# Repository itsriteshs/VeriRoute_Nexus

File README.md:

# PacketFlow ImmuneNet

**TCP/IP for parcels, with an immune system for trust.**

PacketFlow ImmuneNet is a trust-aware logistics protocol for FAR AWAY 2026 Round 1. Modern logistics systems often track claims that a parcel moved. PacketFlow ImmuneNet verifies whether each movement could physically have happened using scan identity, GPS/geofence proof, timestamp and speed plausibility, route graph validity, temperature state, tamper state, hub trust, and live rerouting.

The MVP combines a FastAPI backend, a React/Vite digital twin dashboard, deterministic simulation scenarios, an event ledger, WebSocket live updates, and SmartHub hardware-ready ESP32 assets. The project started as VeriRoute Nexus; the submission-facing product name is **PacketFlow ImmuneNet**.

Final line: **We are not tracking parcels. We are proving movement.**

## Run Locally

Use two terminals.

Terminal 1, backend:

```bash
cd backend
python3 -m venv .venv
source .venv/bin/activate
pip install -r requirements.txt
./run.sh
```

Terminal 2, frontend:

```bash
cd frontend
npm install
npm run dev
```

Open:

```text
http://localhost:5173/dashboard
```

Reset the demo:

```bash
curl -X POST http://localhost:8000/demo/reset
```

Run verification:

```bash
cd backend
source .venv/bin/activate
pytest

cd ../frontend
npm run typecheck
npm run build
```

More detail: [Demo Guide](docs/DEMO_GUIDE.md) and [API Reference](docs/API.md).

## Live Deployment

Full deployment:

```text
https://packetflow-immunenet.vercel.app
```

This Vercel deployment serves both the React/Vite dashboard and the FastAPI backend:

- Frontend: `https://packetflow-immunenet.vercel.app/dashboard`
- Backend health: `https://packetflow-immunenet.vercel.app/api/health`
- Backend docs are still available locally at `http://localhost:8000/docs`; the Vercel demo exposes the API routes under `/api`.

The hosted backend uses Vercel Services and an ephemeral SQLite database in `/tmp`. That is enough for a live hackathon demo with reset/seed flows, but production should move state to Postgres or another managed database.

Deploy commands:

```bash
vercel pull --yes --environment=preview
vercel deploy --prod
```

## 30-Second Explanation

Logistics networks break when scans are trusted blindly. A fake scan, impossible travel speed, wrong geofence, cold-chain breach, or tampered package can make a dashboard look normal while the parcel is compromised. PacketFlow ImmuneNet treats each scan as a movement claim. Proof-of-Movement validates the claim, ImmuneNet blocks or warns on anomalies, the trust ledger updates hub reputation, and PacketFlow chooses the next route based on trust, congestion, SLA, cold-chain needs, cost, and disruption state.

## Problem

- Rigid route plans fail when hubs are overloaded, blocked, or unsafe.
- Tracking systems often record a scan without proving the scanner was physically near the hub.
- Fake scans, clone scans, and impossible movement can pass as normal status updates.
- Cold-chain parcels need temperature-aware routing, not only location updates.
- Logistics networks need hub-level trust scores and auditable proof, not only carrier claims.

## Solution

- **PacketFlow Routing Engine:** dynamic next-hop routing over a hub graph.
- **Proof-of-Movement Ledger:** hash-linked event ledger for accepted, blocked, and rerouted movement claims.
- **ImmuneNet Anomaly Engine:** geofence, speed, graph, clone, cold-chain, tamper, handshake, mesh witness, and statistical checks.
- **AgentOps Disruption Replanner:** deterministic scenario handlers for hub failure, overload, traffic, weather, and temperature breach.
- **SwarmFlow Digital Twin:** React dashboard for route decisions, trust, alerts, metrics, and live events.
- **SmartHub Relay Node:** ESP32/RFID/QR/GPS/temperature/BLE/ESP-NOW-ready hardware layer and simulator.

## Real Vs Simulated

| Boundary | What is included |
| --- | --- |
| Real in MVP | FastAPI endpoints; SQLite/SQLAlchemy state; PacketFlow route scoring; ImmuneNet scan validation; trust updates; ledger hashing; WebSocket broadcasts; React dashboard pages; demo reset/seed/snapshot; hardware scan bridge endpoint. |
| Simulated in MVP | Hub graph, parcel movement scenarios, traffic/weather/hub disruption inputs, digital twin map layout, hardware simulator actions, demo data for `MED-104`. |
| Hardware-ready | ESP32 Smart Relay Hub firmware, Smart Parcel Tag firmware, RFID/QR/GPS/temperature/BLE payload shape, ESP-NOW handshake endpoint, CAD/PCB/pin-map documentation, Python hardware simulator. |
| Future roadmap | Real multi-site deployment, production identity provisioning, carrier integrations, secure device keys, real GPS permission flows at scale, ONDC/e-commerce integration, hosted observability, production auth, and multi-tenant fleet operations. |

More detail: [Feature Status](docs/FEATURE_STATUS.md), [Hardware](docs/HARDWARE.md), and [Simulation](docs/SIMULATION.md).

## Architecture

```mermaid
flowchart LR
  Dashboard[Frontend Dashboard\nReact/Vite Digital Twin]
  ScanPage[Scan Page\nQR/RFID/manual input]
  Twin[SwarmFlow Digital Twin]
  API[FastAPI Backend]
  PacketFlow[PacketFlow Routing Engine]
  ImmuneNet[ImmuneNet Anomaly Engine]
  Ledger[(Trust Ledger\nSQLite + hash chain)]
  WS[WebSocket Live Updates]
  Hardware[SmartHub / ESP32 Layer\nRFID, QR, temp, BLE, ESP-NOW]
  Sim[Simulation Scenario Engine]
  Explain[Optional deterministic explanation layer]

  Dashboard --> API
  ScanPage --> API
  Twin --> API
  Hardware --> API
  Sim --> API
  API --> PacketFlow
  API --> ImmuneNet
  PacketFlow --> Ledger
  ImmuneNet --> Ledger
  API --> WS
  WS --> Dashboard
  API --> Explain
```

More detail: [Architecture](docs/ARCHITECTURE.md).

## System Flow

1. Parcel is created or seeded as `MED-104`.
2. Scan event is submitted from the dashboard, scan page, demo control, or hardware bridge.
3. Proof-of-Movement validates identity, geofence, timestamp/speed plausibility, route graph, temperature, tamper, and optional hardware context.
4. ImmuneNet returns `ACCEPTED`, `WARNING`, `BLOCKED`, `REROUTED`, or `HOLD`.
5. Hub trust score changes and trust history is stored.
6. PacketFlow recalculates route decisions from the current hub.
7. WebSocket broadcasts update the dashboard.
8. Ledger entry is persisted with hash-chain fields.
9. The system accepts, reroutes, blocks, or holds the movement claim.

## Features

| Group | MVP behavior |
| --- | --- |
| PacketFlow Routing Engine | Scores candidate next hops using SLA risk, congestion, trust risk, condition/cold-chain risk, and cost/emission. |
| Proof-of-Movement Scan Validation | Treats every scan as a movement claim and verifies physical plausibility. |
| ImmuneNet Anomaly Engine | Blocks fake scans, clone scans, impossible graph moves, and suspicious geofence/speed failures. |
| AgentOps Disruption Replanner | Replans routes for hub failure, overload, traffic jam, weather risk, and temperature breach scenarios. |
| SwarmFlow Digital Twin | Shows hubs, route path, parcels, alerts, ledger, trust board, and demo controls. |
| Hub Trust Ledger | Stores event history, route decisions, trust score deltas, and ledger hashes. |
| Cold-Chain Breach Handling | Detects hot medicine parcel conditions and prefers cold-chain routing such as `COLD-HUB-C`. |
| Fake Scan / Impossible Movement Blocking | Provides explicit fake, clone, route, and speed scenarios. |
| SmartHub Hardware Interface | Accepts ESP32-native scan payloads and peer handshakes through `/hardware/*`. |
| Demo Scenario Controls | Frontend and scripts trigger reset, scan, reroute, fake scan, breach, and hardware paths. |
| Explainable Decision Panel | Backend returns reasons and candidate score breakdowns for judge-readable decisions. |

More detail: [Feature Status](docs/FEATURE_STATUS.md).

## Demo Scenarios

| Scenario | How to demonstrate |
| --- | --- |
| Normal medicine parcel route | Reset demo, create or seed `MED-104`, submit valid `HUB-A` scan, show `ACCEPTED`, green LED, route decision, and ledger entry. |
| Hub overload reroute | Trigger `POST /scenario/overload-hub` or dashboard overload control, then show AgentOps reroute and updated candidate scores. |
| Fake scan from wrong location | Trigger `POST /scan/fake`, show `BLOCKED`, `fake_scan_blocked`, trust decay, and red alert. |
| Impossible movement / speed violation | Submit scans too close in time across distant hubs or use clone scenario; show speed/clone failure. |
| Cold-chain breach reroute | Trigger `POST /scenario/temp-breach` with temperature above limit; show cold-chain alert and route via cold-capable hubs. |
| Trust score decay | Run fake/tamper/blocked events and open Trust Board or `/trust/history/HUB-C`. |
| AgentOps disruption replanning | Trigger fail hub, traffic jam, or weather risk scenario and show old route vs new route. |
| Fixed-route comparison vs PacketFlow | Use route decision candidate scores to explain why dynamic routing avoids unsafe or overloaded paths. |

More detail: [Demo Guide](docs/DEMO_GUIDE.md).

## API Routes

The backend is FastAPI and the following table is generated from the actual route modules in `backend/app/routes`. More request/response examples are in [API Reference](docs/API.md).

| Method | Path | Purpose | Request body example | Response example | Used by |
| --- | --- | --- | --- | --- | --- |
| GET | `/health` | Health check | None | `{"status":"ok"}` | Frontend, smoke checks |
| GET | `/ready` | Readiness with dependency checks | None | `{"status":"ready"}` | Operators |
| POST | `/demo/seed` | Seed deterministic demo state | None | `{"status":"seeded"}` | Demo |
| POST | `/demo/reset` | Reset demo database state | None | `{"status":"seeded"}` | Demo, scripts |
| GET | `/demo/snapshot` | Return dashboard state bundle | None | hubs, edges, parcel, latest route, metrics | Frontend |
| POST | `/demo/validate` | Run backend demo validation | `{}` | validation result | Demo |
| POST | `/demo/run/main-wow` | Run scripted demo sequence | `{}` | scenario summary | Demo |
| POST | `/demo/toggle-sync` | Toggle offline sync simulation | `{}` | sync status | Demo |
| POST | `/demo/flush-sync` | Mark unsynced events synced | `{}` | flush count | Demo |
| GET | `/hubs` | List hub graph nodes | None | `{"hubs":[...]}` | Frontend |
| GET | `/edges` | List graph edges | None | `{"edges":[...]}` | Frontend |
| POST | `/parcels` | Create/upsert parcel and initial route | `{"id":"MED-104","source_hub":"HUB-A"}` | parcel and initial route | Frontend/demo |
| GET | `/parcels` | List parcels | None | `{"parcels":[...]}` | Frontend |
| GET | `/parcels/{parcel_id}` | Parcel detail and latest events | None | parcel, latest events | Frontend |
| GET | `/ledger/events` | List event ledger, optional filters | Query params | `{"events":[...]}` | Frontend/demo |
| GET | `/ledger/parcel/{parcel_id}` | Parcel-specific ledger and proof context | None | events, route, trust, immune checks | Frontend |
| GET | `/ledger/verify/{parcel_id}` | Verify event hash chain | None | validity summary | Frontend/demo |
| GET | `/metrics` | Return demo impact metrics | None | metric counters | Frontend |
| POST | `/route/next-hop` | Calculate PacketFlow next hop | `{"parcel_id":"MED-104","current_hub":"HUB-A"}` | route decision | Frontend/demo |
| GET | `/route/decisions` | List route decisions | None | route history | Demo/docs |
| GET | `/route/decisions/{parcel_id}` | List route decisions for parcel | None | route history | Demo/docs |
| GET | `/route/{parcel_id}` | Latest route for parcel | None | route decision | Frontend |
| POST | `/scan` | Submit movement claim | `{"parcel_id":"MED-104","hub_id":"HUB-A","gps":{"lat":11.0168,"lng":76.9558}}` | scan decision | Frontend/demo |
| POST | `/scan/fake` | Simulate fake scan | `{"parcel_id":"MED-104","claimed_hub":"HUB-C","fake_gps":{"lat":11.1,"lng":77.1}}` | blocked decision | Demo |
| POST | `/scan/clone` | Simulate clone scan | `{"parcel_id":"MED-104","first_hub":"HUB-B","second_hub":"HUB-D"}` | blocked decision | Demo |
| POST | `/scan/tamper` | Simulate tamper scan | `{"parcel_id":"MED-104","hub_id":"HUB-C","tamper":true}` | hold decision | Demo |
| GET | `/trust/hubs` | Hub trust board | None | `{"hubs":[...]}` | Frontend |
| GET | `/trust/history/{hub_id}` | Trust score history | None | `{"history":[...]}` | Frontend |
| POST | `/scenario/fail-hub` | Simulate failed hub | `{"hub_id":"HUB-B","parcel_id":"MED-104"}` | old/new routes | Demo |
| POST | `/scenario/overload-hub` | Simulate congestion | `{"hub_id":"HUB-B","congestion":0.95}` | old/new routes | Demo |
| POST | `/scenario/traffic-jam` | Simulate risky edge | `{"from_hub":"HUB-B","to_hub":"HUB-E","traffic_risk":0.95}` | old/new routes | Demo |
| POST | `/scenario/weather-risk` | Simulate weather risk | `{"from_hub":"HUB-B","to_hub":"HUB-E","weather_risk":0.9}` | old/new routes | Demo |
| POST | `/scenario/temp-breach` | Simulate cold-chain breach | `{"parcel_id":"MED-104","hub_id":"HUB-A","temperature_c":29.2}` | reroute/alert result | Demo |
| POST | `/hardware/scan` | Accept ESP32/native scan payload | `{"device_id":"ESP32-HUB-A-01","hub_id":"HUB-A","parcel_id":"MED-104","lat":11.0168,"lng":76.9558}` | hardware scan decision | Hardware/simulator |
| POST | `/hardware/p2p-handshake` | Log ESP-NOW relay handshake | `{"sender_hub":"HUB-A","receiver_hub":"HUB-B","parcel_id":"MED-104","message_type":"TRUST_SYNC"}` | event id and reason | Hardware/simulator |
| GET | `/ws/status` | WebSocket availability | None | connection count | Frontend |
| WS | `/ws` | Live event stream | WebSocket | event envelope | Frontend |
| GET | `/` | Root project metadata | None | project summary | Browser |

## WebSocket Events

WebSocket messages are envelopes: `{"type":"event_type","timestamp":"...","payload":{...}}`.

Implemented event types include `parcel_created`, `scan_received`, `movement_accepted`, `movement_blocked`, `movement_warning`, `route_decision`, `reroute_triggered`, `trust_updated`, `temperature_breach`, `fake_scan_blocked`, `clone_scan_blocked`, `tamper_alert`, `hub_failed`, `hub_overloaded`, `traffic_jam`, `weather_risk`, `immune_alert`, `p2p_handshake`, `metrics_updated`, `demo_reset`, `hardware_scan_received`, `hardware_scan_completed`, `ble_tag_detected`, and `esp_now_prior_acceptance`.

The `simulation_update` name is not a separate current event; simulation changes are emitted through scenario-specific events plus `reroute_triggered` and `metrics_updated`.

## Full Setup

Clone and enter the repo:

```bash
git clone https://github.com/itsriteshs/VeriRoute_Nexus.git
cd VeriRoute_Nexus
```

Backend:

```bash
cd backend
python3 -m venv .venv
source .venv/bin/activate
pip install -r requirements.txt
./run.sh
```

Frontend:

```bash
cd frontend
npm install
npm run dev
```

Reset demo data:

```bash
curl -X POST http://localhost:8000/demo/reset
```

Run tests and builds:

```bash
cd backend
source .venv/bin/activate
pytest

cd ../frontend
npm run typecheck
npm run build
```

Optional hardware simulator:

```bash
cd hardware_submission/simulation
python3 simulate_hardware.py
```

More detail: [Hardware](docs/HARDWARE.md) and [Demo Guide](docs/DEMO_GUIDE.md).

## Environment Variables

| File | Variable | Required | Purpose |
| --- | --- | --- | --- |
| `.env.example` | `BACKEND_URL` | Optional | Root-level backend URL hint for scripts/docs. |
| `.env.example` | `FRONTEND_URL` | Optional | Root-level frontend URL hint. |
| `.env.example` | `DEMO_MODE` | Optional | Marks local deterministic demo mode. |
| `backend/.env.example` | `DATABASE_URL` | Optional | Intended DB URL; current app uses SQLite config from backend settings. |
| `backend/.env.example` | `FRONTEND_ORIGIN` | Optional | CORS/documentation hint. |
| `backend/.env.example` | `DEMO_MODE` | Optional | Demo mode flag. |
| `frontend/.env.example` | `VITE_API_BASE_URL` | Optional | Frontend API base, defaults to `http://localhost:8000`. |
| `frontend/.env.example` | `VITE_WS_URL` | Optional | WebSocket URL, defaults to `ws://localhost:8000/ws`. |

No AI API key is required for the MVP. Explanations are deterministic/template-based in the backend.

## Project Structure

```text
backend/              FastAPI app, SQLAlchemy models, engines, routes, schemas, tests, scripts
frontend/             React/Vite dashboard, digital twin, pages, components, API client
hardware_submission/  ESP32 firmware, simulator, CAD, PCB, wiring, hardware documentation
data/                 Demo hubs, edges, parcels, scenarios
docs/                 Judge-facing docs, architecture, API, simulation, hardware, evaluation
presentation/         Demo script, backup plan, Q&A, screenshots checklist
scripts/              Root helper scripts for backend/frontend/reset/seed
API_CONTRACT.md       Original API coordination contract
DEMO_RUNBOOK.md       Existing demo runbook
PROJECT_STATUS.md     Current project status notes
what_is_done_*.md     Team member progress trackers
```

The root also contains team workflow and integration notes such as `TEAM_WORKFLOW.md`, `INTEGRATION_CHECKLIST.md`, `PRIVACY_AND_TRUST.md`, and `CONTRIBUTING.md`. These are supporting documents; the fastest judge path is this README plus the focused files in `docs/`.

## Screenshots

See [Screenshots To Add](docs/screenshots/README.md) for the screenshot capture list. Judges should expect dashboard overview, digital twin, fake scan blocked, cold-chain breach, trust ledger, API docs, and hardware setup screenshots.

## Reliability And Fallback Plan

- If RFID fails, use the frontend scan page at `/scan/HUB-A?parcel_id=MED-104`, the dashboard controls, or direct `POST /scan`.
- If GPS permission fails, use demo coordinates in the request body.
- If temperature sensor fails, trigger deterministic breach through `/scenario/temp-breach`.
- If the AI explanation layer fails, use deterministic backend reason strings.
- If hardware fails, run the software-only dashboard and `hardware_submission/simulation/simulate_hardware.py`.
- If internet fails, run the full localhost demo with SQLite and Vite.

## Scalability

PacketFlow ImmuneNet can start as a campus or warehouse pilot, then expand to a city micro-hub network, multi-carrier parcel exchange, ONDC/e-commerce logistics, pharma/cold-chain compliance, disaster relief routing, and cross-border checkpoint logistics. The protocol concept scales because it separates proof ingestion, movement validation, hub trust, and routing decisions.

More detail: [Simulation](docs/SIMULATION.md) and [Architecture](docs/ARCHITECTURE.md).

## Privacy And Safety

The system verifies logistics events, not workers or customers continuously. It stores parcel IDs, scan-time scanner/hub location, temperature state, event reasons, and hub trust scores. It does not need continuous personal location tracking. In production, device identity and parcel IDs should be scoped, rotated where appropriate, and governed by retention rules.

## More Docs

- [Architecture](docs/ARCHITECTURE.md)
- [API Reference](docs/API.md)
- [Demo Guide](docs/DEMO_GUIDE.md)
- [Simulation](docs/SIMULATION.md)
- [Hardware](docs/HARDWARE.md)
- [Feature Status](docs/FEATURE_STATUS.md)
- [Screenshots To Add](docs/screenshots/README.md)

**We are not tracking parcels. We are proving movement.**

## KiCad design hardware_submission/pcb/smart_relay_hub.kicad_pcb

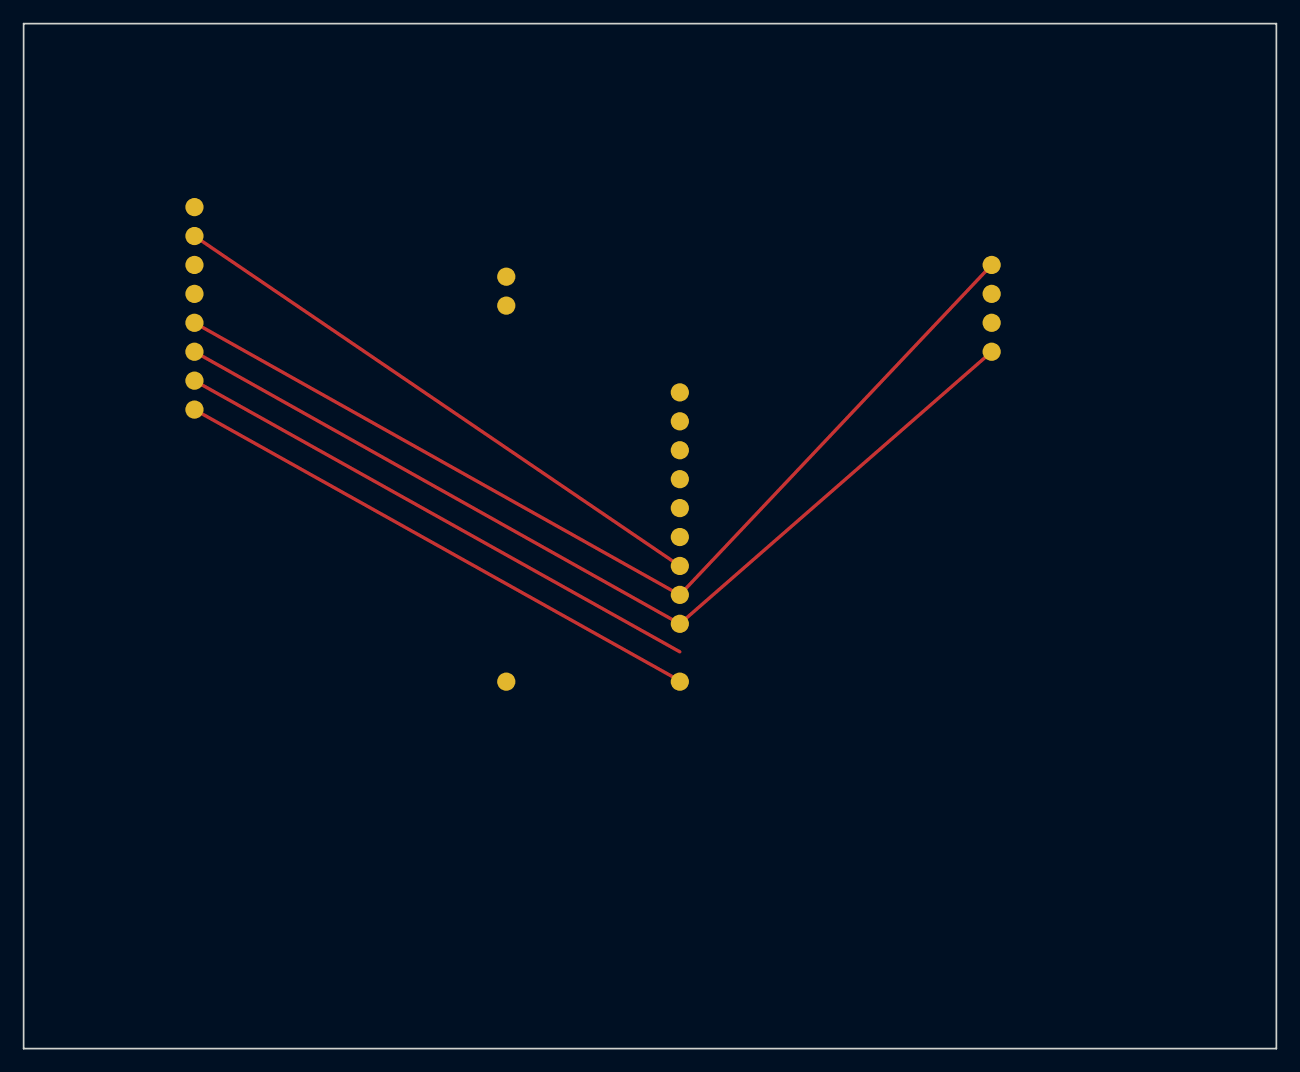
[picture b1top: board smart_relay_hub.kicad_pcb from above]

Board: 0 copper layers, 110.0 x 90.0 mm, 3 parts (0 on the bottom side), 9 nets.

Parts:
DISP1: SSD1306 OLED; PinHeader_1x04_P2.54mm_Vertical
U1: ESP32 DevKit v1; DIP-30_W15.24mm
U2: RC522 RFID; PinHeader_1x08_P2.54mm_Vertical

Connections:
+3V3: DISP1.2, U1.1, U2.1
GND: DISP1.1, U1.2, U1.15, U1.16, U2.3, U2.4
I2C_SCL: DISP1.3, U1.23
I2C_SDA: DISP1.4, U1.24
RFID_CS: U1.18, U2.8
RFID_RST: U1.22, U2.2
SPI_MISO: U1.20, U2.5
SPI_MOSI: U1.21, U2.6
SPI_SCK: U1.19, U2.7

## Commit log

2026-06-07 Initial project setup
2026-06-07 chore: initialize VeriRoute Nexus monorepo structure for Team Aristotle
2026-06-08 Build PacketFlow frontend dashboard pages
2026-06-08 Polish PacketFlow mission-control frontend
2026-06-08 Build backend phases 1 through 4
2026-06-08 Phase 7, 8 & 9: Complete Hardware Integration, Diagnostic Endpoints & Demo Hardening
2026-06-08 feat(frontend): integrate react dashboard with fastapi and websocket live state
2026-06-08 final
2026-06-08 added
2026-06-08 Integrate backend and frontend, fix temp-breach route fallback, and clean up JSX files
2026-06-08 Enable WAL mode and update database models for Bayesian/cryptographic schema
2026-06-08 Implement Bayesian trust updates and SHA-256 event chaining
2026-06-08 Implement Zero-Trust Handshake, Proximity BLE Mesh, Z-Score anomaly detection, and WHO MKT cold-chain math
2026-06-08 Integrate offline sync queue endpoints and React hook state handlers
2026-06-13 refactor(hardware): update docs to align with v2 PCBs and STEP CAD files, fix simulator
2026-06-14 final commit
2026-06-14 vercel update
2026-06-14 docs: add screenshots for submission
